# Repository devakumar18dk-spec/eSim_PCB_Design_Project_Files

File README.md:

<div align="center">

# ⚡ Enhanced Power Supply ESP32

### Wide-Input (7–24 V) ESP32-C3 Development Board — A Complete Embedded Hardware Platform

**Designed & Simulated in FOSSEE eSim (KiCad-based workflow)**

</div>

<br>

<p align="center"><sub>🧊 3D render of the routed 4-layer board — ESP32-C3-WROOM-02, USB-C, DC barrel jack, and dual GPIO headers.</sub></p>

<div align="center">

`Power In (7–24V)` → `Protection` → `5V Buck` → `3.3V LDO` → `ESP32-C3` ⚡

</div>

```bash
git clone https://github.com/devakumar18dk-spec/eSim_PCB_Design_Project_Files.git
```

---

## 📖 Table of Contents

- [Overview](#-overview)
- [Highlights & Features](#-highlights--features)
- [System Architecture](#-system-architecture)
- [Power Architecture](#-power-architecture)
- [USB-C Interface](#-usb-c-interface)
- [Boot & Reset Control](#-boot--reset-control)
- [RTC Timing](#-rtc-timing)
- [GPIO Expansion](#-gpio-expansion)
- [PCB Design (4-Layer)](#-pcb-design-4-layer)
- [📐 Schematic](#-schematic)
- [🖼 PCB Layout](#-pcb-layout)
- [Technical Specifications](#-technical-specifications)
- [Design Verification Checklist](#-design-verification-checklist)
- [Hardware Bring-Up Sequence](#-hardware-bring-up-sequence)
- [Design Workflow](#-design-workflow)
- [Repository Structure](#-repository-structure)
- [Getting Started](#-getting-started)
- [Contributing](#-contributing)
- [License](#-license)
- [Acknowledgements](#-acknowledgements)

---

## 🧭 Overview

This project presents the design and PCB implementation of a custom **ESP32-C3-based development board**, engineered end-to-end using the **FOSSEE eSim electronics design environment**. Rather than functioning as a simple ESP32 breakout, this board is architected as a **complete embedded hardware platform** — integrating wide-range DC power input, robust input protection, two-stage voltage regulation, USB-C connectivity with ESD protection, hardware boot/reset control, RTC timing, and expandable GPIO — all realized on a **four-layer PCB**.

> **Design philosophy:** protect first, convert efficiently, regulate cleanly, then compute. Every subsystem exists to deliver a stable, low-noise supply and a reliable interface to the ESP32-C3.

```
7–24 V DC  →  Protection  →  5 V Buck  →  3.3 V LDO  →  ESP32-C3
```

---

## ✨ Highlights & Features

<table>
<tr>
<td width="50%" valign="top">

### 🔋 Power System
- Wide **7 V – 24 V DC** input range
- Reverse-polarity protection via **P-channel MOSFET**
- **TVS/Zener** transient (surge) protection
- Two-stage regulation: **Buck (5 V) → LDO (3.3 V)**
- Local bulk + high-frequency decoupling at the MCU

### 🔌 Connectivity
- **USB Type-C** interface (16-pin receptacle)
- CC1/CC2 configuration resistors (device/sink mode)
- Dedicated **USBLC6-2SC6** ESD protection on D+/D−
- USB used strictly for data/programming — **not** primary power

</td>
<td width="50%" valign="top">

### 🧠 Control & Expansion
- **ESP32-C3-WROOM-02** central controller
- Dedicated **EN (Reset)** and **IO9 (Boot)** push buttons
- **32.768 kHz RTC crystal** for low-power timekeeping
- **2 × 8-pin, 2.54 mm** GPIO expansion headers

### 🧱 PCB Engineering
- **4-layer stack-up**: Power / Signal / Mixed / Ground
- Dedicated **ESP32 antenna keep-out zone**
- Functionally-grouped component placement
- Continuous ground plane for low-impedance return paths

</td>
</tr>
</table>

---

## 🏗 System Architecture

The board is organized into five functional sections: **Power**, **USB-C**, **Main Controller**, **Boot/Reset**, and **GPIO/Expansion**.

```
                  ESP32-C3 DEVELOPMENT BOARD
                           │
       ┌───────────────────┼───────────────────┐
       │                   │                   │
       ▼                   ▼                   ▼
 POWER SYSTEM         USB-C SYSTEM       CONTROL / I/O
       │                   │                   │
  7–24 V DC           USB Type-C          Boot Button
       │                   │               Reset Button
       ▼                   │                   │
 Input Protection          │                   │
       │                   │                   │
       ▼                   ▼                   ▼
 5 V Buck              ESD Protection      ESP32-C3
       │                   │                   │
       ▼                   ▼              GPIO Headers
 5 V Rail              USB D+/D−
       │
       ▼
 3.3 V LDO
       │
       ▼
  +3.3 V Rail
       │
       ▼
  ESP32-C3 WROOM-02
       │
       └── 32.768 kHz RTC Crystal
```

---

## 🔋 Power Architecture

Every subsystem on this board depends on a stable, protected supply — so power is treated as the primary design driver, not an afterthought.

### Main Power Path

```
DC Input → Protection → Buck Converter (5 V) → LDO (3.3 V) → ESP32-C3
```

The board deliberately avoids converting the full 7–24 V range directly to 3.3 V with a linear regulator. Instead, a **switching regulator** absorbs the large voltage difference efficiently, while an **LDO** performs final, low-noise regulation — the right tool for each job.

<details>
<summary><b>🛡️ Input Protection — click to expand</b></summary>

<br>

| Function | Component | Behavior |
|---|---|---|
| Transient protection | TVS / Zener network | Inactive under normal operation; clamps excess voltage during spikes |
| Reverse-polarity protection | P-channel MOSFET (STN3P6F6) | Low-resistance conduction on correct polarity; blocks reverse voltage |

```
Correct polarity          Incorrect polarity
      │                          │
      ▼                          ▼
P-MOSFET conducts          MOSFET blocks
      │                          │
      ▼                          ▼
Power reaches regulator    Downstream circuitry protected
```

A P-MOSFET is used instead of a conventional diode because it offers **much lower conduction loss**.

</details>

<details>
<summary><b>⚙️ 5 V Buck Conversion — click to expand</b></summary>

<br>

The protected input feeds the **LMR50410-Q1** switching regulator, which converts **7–24 V → 5 V** by transferring energy through controlled switching rather than dissipating the difference as heat.

**Supporting components:** 4.7 µH inductor · bootstrap capacitor · input/output capacitors · feedback resistor network · 10 µF local input capacitor (placed close to the regulator to keep the high-frequency current loop compact).

```
7–24 V ─► Switching Node ─► 4.7 µH Inductor ─► Output Filter ─► 5 V
```

</details>

<details>
<summary><b>🎯 3.3 V LDO Post-Regulation — click to expand</b></summary>

<br>

The 5 V rail feeds an **LM1117-3.3** LDO, which handles only the small **5 V → 3.3 V** step. This division of labor means:

| Stage | Responsibility |
|---|---|
| Buck | Efficient large voltage conversion (7–24 V → 5 V) |
| LDO | Final clean regulation, ripple attenuation, low-impedance supply |

The LDO also provides power-supply rejection within its effective PSRR band, attenuating residual switching ripple before it reaches the ESP32-C3.

</details>

<details>
<summary><b>📎 MCU Decoupling — click to expand</b></summary>

<br>

Local **4.7 µF** (bulk) and **100 nF** (high-frequency) capacitors sit right at the ESP32-C3 supply pins, supplying transient current locally instead of forcing it through long PCB traces from the regulator — reducing supply impedance seen by the controller.

</details>

<div align="right"><sub><a href="#-enhanced-power-supply-esp32">⬆ back to top</a></sub></div>

---

## 🔌 USB-C Interface

The USB-C section is an **independent communication interface**, cleanly separated from the main power path.

| Element | Detail |
|---|---|
| Connector | USB Type-C, 16-pin |
| CC configuration | 2 × 5.1 kΩ on CC1/CC2 → configures board as USB-C sink/device |
| ESD protection | USBLC6-2SC6, placed near the connector |
| Role | Data / programming only — **not** the primary power source |

```
External USB Connector → ESD Protection → ESP32-C3
```

Keeping USB power and main DC power separate lets the board run continuously from the 7–24 V input while still using USB freely for programming and debugging.

---

## 🛠 Boot & Reset Control

| Button | Signal | Function |
|---|---|---|
| Reset | EN | 10 kΩ pull-up; pressing forces EN low and resets the MCU |
| Boot | IO9 | 10 kΩ pull-up; pressing changes boot-strap state to enter programming mode |

```
USB connected → Hold BOOT → Reset ESP32-C3 → Enters programming mode
```

---

## ⏱ RTC Timing

A **32.768 kHz crystal** provides an external low-frequency timing reference for the ESP32-C3 RTC. It's placed close to the module to minimize parasitics and kept away from the buck converter's switching node to avoid noise coupling.

---

## 🧩 GPIO Expansion

Two **8-pin, 2.54 mm pitch headers** expose selected ESP32-C3 GPIOs, turning the board into a reusable development platform for sensors, LEDs, displays, communication modules, and breadboard prototyping.

---

## 🧱 PCB Design (4-Layer)

| Layer | Purpose |
|---|---|
| **F.Cu** (Top) | Power distribution & primary component routing |
| **In1.Cu** | Signal routing (GPIO fan-out from the ESP32-C3) |
| **In2.Cu** | Mixed-purpose routing / secondary distribution |
| **B.Cu** (Bottom) | Continuous ground plane |

<details>
<summary><b>📍 Component Placement Strategy</b></summary>

<br>

| Region | Contents | Rationale |
|---|---|---|
| Upper | ESP32-C3 module, antenna toward board edge | Unobstructed RF environment |
| Central | Buck converter, LDO, protection circuitry, USB-C | Short, low-impedance power connections |
| Lower | Boot/Reset buttons | User accessibility |
| Sides | GPIO headers (left & right) | Convenient external interfacing |

</details>

<details>
<summary><b>📡 Antenna Keep-Out</b></summary>

<br>

A clearly defined **keep-out zone** sits above the ESP32-C3 module — no copper, tracks, or vias are routed through this area, per module manufacturer guidance, to prevent detuning or shielding the integrated antenna.

</details>

<details>
<summary><b>🧵 Routing & Grounding Philosophy</b></summary>

<br>

- **High-current power paths** — short and comparatively wide (DC input, MOSFET, buck, inductor, 5 V rail, LDO)
- **Switching node** — kept as small as practical to limit EMI coupling
- **USB D+/D−** — routed as a matched differential pair, ESD device close to the connector
- **RTC crystal traces** — short, isolated from switching noise
- **Ground plane (B.Cu)** — continuous reference plane minimizing loop area, EMI, and supply noise — especially important given the ESP32-C3's onboard radio

</details>

<details>
<summary><b>🌡️ Thermal Considerations</b></summary>

<br>

Primary heat sources are the **buck converter**, **LDO**, and **protection MOSFET**. The LDO has the most predictable thermal profile since it dissipates the 5 V→3.3 V difference directly — adequate copper area is provided around its thermal pads per datasheet recommendations.

</details>

---

## 📐 Schematic

<div align="center">

| 🔋 Input → 5V → 3.3V | 🔌 USB-C & ESD | 🛠 Boot & Reset | 🧠 Main Controller | 🧩 GPIOs |
|:---:|:---:|:---:|:---:|:---:|
| ST6P3F6, LMR50410-Q1, LM1117-3.3 | USB-C receptacle, USBLC6-2SC6 | EN & IO9 push buttons | ESP32-C3-WROOM-02 | 2 × 8-pin headers |

</div>

<p align="center"><sub>📄 Captured entirely in <b>FOSSEE eSim</b> — five functional blocks laid out for clarity: power regulation (top), USB-C/protection, boot/reset, and GPIO breakout (bottom row), with the main ESP32-C3 controller on the right.</sub></p>

---

## 🖼 PCB Layout

The board is routed across **four copper layers**, each with a distinct role. Toggle through the stack below — every view shares the same silhouette so you can trace a single net (e.g. GND) from top to bottom.

<table align="center">
<tr>
<th align="center">🟥 F.Cu — Power / Top Layer</th>
<th align="center">🟩 In1.Cu — Signal Layer</th>
</tr>
<tr>
<td></td>
<td></td>
</tr>
<tr>
<td align="center"><sub>Primary power distribution & component-side routing</sub></td>
<td align="center"><sub>ESP32-C3 GPIO fan-out toward J3 / J4 headers</sub></td>
</tr>
<tr>
<th align="center">🟧 In2.Cu — Mixed Routing Layer</th>
<th align="center">🟦 B.Cu — Ground Plane</th>
</tr>
<tr>
<td></td>
<td></td>
</tr>
<tr>
<td align="center"><sub>Secondary power/signal distribution channel</sub></td>
<td align="center"><sub>Continuous ground reference plane</sub></td>
</tr>
</table>

> 🛰️ **Antenna Keep-Out Zone** — visible as the hatched `KEEP-OUT ZONE / Antenna` region above the ESP32-C3 module on every layer. No copper, tracks, or vias are routed through this area to protect RF performance.

<details>
<summary><b>📊 Routing Stats (from PCB editor)</b></summary>

<br>

| Metric | Count |
|---|---|
| Pads | 151 |
| Vias | 102 |
| Nets | 586 |
| Unrouted | 0 ✅ |

</details>

<div align="right"><sub><a href="#-enhanced-power-supply-esp32">⬆ back to top</a></sub></div>

---

## 📋 Technical Specifications

| Specification | Design |
|---|---|
| MCU | ESP32-C3-WROOM-02 |
| Main DC input | 7–24 V |
| Primary power connector | DC input connector |
| Input protection | TVS/Zener + P-channel MOSFET |
| Reverse polarity protection | STN3P6F6 P-MOSFET |
| Buck regulator | LMR50410-Q1 |
| Buck output | 5 V |
| Buck inductor | 4.7 µH |
| Post-regulator | LM1117-3.3 |
| Final logic rail | 3.3 V |
| RTC reference | 32.768 kHz crystal |
| USB connector | USB Type-C, 16-pin |
| USB CC resistors | 5.1 kΩ × 2 |
| USB ESD protection | USBLC6-2SC6 |
| Reset control | EN push button |
| Boot control | IO9 push button |
| Button pull-ups | 10 kΩ |
| GPIO expansion | 2 × 8-pin headers |
| GPIO header pitch | 2.54 mm |
| PCB structure | 4-layer |
| F.Cu | Primary power / component routing |
| In1.Cu | Signal routing |
| In2.Cu | Mixed routing / distribution |
| B.Cu | Ground plane |
| RF provision | ESP32 antenna keep-out |
| Design environment | FOSSEE eSim / KiCad-based workflow |

---

## ✅ Design Verification Checklist

<table>
<tr>
<td width="50%" valign="top">

**Schematic Checks**
- [ ] All power nets verified
- [ ] 3.3 V connections verified
- [ ] 5 V connections verified
- [ ] All ground connections verified
- [ ] ESP32-C3 power pins checked
- [ ] Boot strapping verified
- [ ] EN/reset circuitry verified
- [ ] USB D+/D− connections verified
- [ ] USB CC resistors verified
- [ ] No unintended VBUS-to-3.3 V paths

</td>
<td width="50%" valign="top">

**PCB Checks**
- [ ] Design Rule Check (DRC) passed
- [ ] Track widths verified
- [ ] Clearances verified
- [ ] Via placement checked
- [ ] Copper-zone connections checked
- [ ] Antenna keep-out respected
- [ ] Silkscreen overlaps checked
- [ ] Connector orientation verified
- [ ] Footprint pin numbering verified
- [ ] Mounting/mechanical dimensions verified

</td>
</tr>
</table>

<div align="right"><sub><a href="#-enhanced-power-supply-esp32">⬆ back to top</a></sub></div>

---

## 🧪 Hardware Bring-Up Sequence

> Do **not** connect the ESP32 module immediately after fabrication — follow a controlled sequence.

| Step | Test | Expected Result |
|---|---|---|
| 1 | Input protection | Protected input rail stable across 7–24 V |
| 2 | Buck converter | ~**+5 V** at buck output (before connecting downstream circuitry) |
| 3 | LDO | ~**+3.3 V** at LDO output |
| 4 | MCU power | ESP32-C3 receives correct 3.3 V supply |
| 5 | Reset | Pressing EN resets the MCU |
| 6 | Boot | IO9 + reset sequencing enters programming mode |
| 7 | USB | USB enumeration / programming succeeds |
| 8 | GPIO | Expansion headers verified with simple GPIO firmware |
| 9 | RTC | 32.768 kHz RTC functionality confirmed |

---

## 🔁 Design Workflow

```
System Requirements → Circuit Architecture → Component Selection
        → Schematic Capture (eSim) → Electrical Connectivity Verification
        → Footprint Assignment → PCB Layout → 4-Layer Stack-up
        → Component Placement → Power Routing → Signal Routing
        → Ground Plane → Antenna Keep-Out → Design Rule Check
        → Gerber / Manufacturing Files → PCB Fabrication → Hardware Testing
```

---

## 🗂 Repository Structure

```
eSim_PCB_Design_Project_Files/
├── assets/
│   └── images/
│       ├── board-render.png       # 3D render
│       ├── schematic.png          # Full eSim schematic
│       ├── pcb-layout-top.png     # F.Cu — power layer
│       ├── pcb-layout-in1.png     # In1.Cu — signal layer
│       ├── pcb-layout-in2.png     # In2.Cu — mixed layer
│       └── pcb-layout-bottom.png  # B.Cu — ground plane
├── hardware/
│   ├── schematic/          # eSim / KiCad schematic project files
│   ├── pcb/                # PCB layout project files
│   └── gerbers/            # Manufacturing output (Gerbers, drill files, BOM)
├── docs/
│   └── technical-report.md # Full design & verification report
├── firmware/                # (optional) example/bring-up firmware
├── LICENSE
└── README.md
```

---

## 🚀 Getting Started

1. **Clone the repository**
   ```bash
   git clone https://github.com/devakumar18dk-spec/eSim_PCB_Design_Project_Files.git
   cd eSim_PCB_Design_Project_Files
   ```
2. **Open the schematic/PCB** in FOSSEE eSim or KiCad from the `hardware/` directory.
3. **Review the Gerbers** in `hardware/gerbers/` before sending to fabrication.
4. **Follow the [Hardware Bring-Up Sequence](#-hardware-bring-up-sequence)** after assembly.
5. **Flash firmware** over USB-C once power rails are verified.

---

## 🤝 Contributing

Contributions, issues, and design suggestions are welcome! Feel free to open a pull request or start a discussion if you'd like to improve the power architecture, layout, or documentation.

---

## 📄 License

This project is released under the **MIT License** — see [`LICENSE`](LICENSE) for details. *(Update if a different license applies.)*

---

## 🙌 Acknowledgements

- **FOSSEE eSim** — schematic capture and simulation environment
- **KiCad** — PCB layout workflow
- **Espressif Systems** — ESP32-C3-WROOM-02 module

---

<div align="center">

### 🧩 Built as a complete embedded hardware platform — not just an ESP32 carrier board.

**Wide-range power management · Protection · Wireless processing · USB-C · Hardware boot control · RTC · Expandable I/O**
**— all in a single four-layer PCB.**

**⭐ If this project helped you, consider starring the repository!**

[⬆ Back to top](#-enhanced-power-supply-esp32)

</div>

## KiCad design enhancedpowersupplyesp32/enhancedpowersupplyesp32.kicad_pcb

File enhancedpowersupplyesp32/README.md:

<div align="center">

# ⚡ ESP32-C3 Wide-Input Development Board

### A Complete Embedded Hardware Platform — Not Just a Breakout Board

**Designed & Simulated in FOSSEE eSim (KiCad-based workflow)**

</div>

<br>

<p align="center"><sub>🧊 3D render of the routed 4-layer board — ESP32-C3-WROOM-02, USB-C, DC barrel jack, and dual GPIO headers.</sub></p>

<div align="center">

`Power In` → `Protection` → `5V Buck` → `3.3V LDO` → `ESP32-C3` ⚡

</div>

---

## 📖 Table of Contents

- [Overview](#-overview)
- [Highlights & Features](#-highlights--features)
- [System Architecture](#-system-architecture)
- [Power Architecture](#-power-architecture)
- [USB-C Interface](#-usb-c-interface)
- [Boot & Reset Control](#-boot--reset-control)
- [RTC Timing](#-rtc-timing)
- [GPIO Expansion](#-gpio-expansion)
- [PCB Design (4-Layer)](#-pcb-design-4-layer)
- [📐 Schematic](#-schematic)
- [🖼 PCB Layout](#-pcb-layout)
- [Technical Specifications](#-technical-specifications)
- [Design Verification Checklist](#-design-verification-checklist)
- [Hardware Bring-Up Sequence](#-hardware-bring-up-sequence)
- [Design Workflow](#-design-workflow)
- [Repository Structure](#-repository-structure)
- [Getting Started](#-getting-started)
- [Contributing](#-contributing)
- [License](#-license)
- [Acknowledgements](#-acknowledgements)

---

## 🧭 Overview

This project presents the design and PCB implementation of a custom **ESP32-C3-based development board**, engineered end-to-end using the **FOSSEE eSim electronics design environment**. Rather than functioning as a simple ESP32 breakout, this board is architected as a **complete embedded hardware platform** — integrating wide-range DC power input, robust input protection, two-stage voltage regulation, USB-C connectivity with ESD protection, hardware boot/reset control, RTC timing, and expandable GPIO — all realized on a **four-layer PCB**.

> **Design philosophy:** protect first, convert efficiently, regulate cleanly, then compute. Every subsystem exists to deliver a stable, low-noise supply and a reliable interface to the ESP32-C3.

```
7–24 V DC  →  Protection  →  5 V Buck  →  3.3 V LDO  →  ESP32-C3
```

---

## ✨ Highlights & Features

<table>
<tr>
<td width="50%" valign="top">

### 🔋 Power System
- Wide **7 V – 24 V DC** input range
- Reverse-polarity protection via **P-channel MOSFET**
- **TVS/Zener** transient (surge) protection
- Two-stage regulation: **Buck (5 V) → LDO (3.3 V)**
- Local bulk + high-frequency decoupling at the MCU

### 🔌 Connectivity
- **USB Type-C** interface (16-pin receptacle)
- CC1/CC2 configuration resistors (device/sink mode)
- Dedicated **USBLC6-2SC6** ESD protection on D+/D−
- USB used strictly for data/programming — **not** primary power

</td>
<td width="50%" valign="top">

### 🧠 Control & Expansion
- **ESP32-C3-WROOM-02** central controller
- Dedicated **EN (Reset)** and **IO9 (Boot)** push buttons
- **32.768 kHz RTC crystal** for low-power timekeeping
- **2 × 8-pin, 2.54 mm** GPIO expansion headers

### 🧱 PCB Engineering
- **4-layer stack-up**: Power / Signal / Mixed / Ground
- Dedicated **ESP32 antenna keep-out zone**
- Functionally-grouped component placement
- Continuous ground plane for low-impedance return paths

</td>
</tr>
</table>

---

## 🏗 System Architecture

The board is organized into five functional sections: **Power**, **USB-C**, **Main Controller**, **Boot/Reset**, and **GPIO/Expansion**.

```
                  ESP32-C3 DEVELOPMENT BOARD
                           │
       ┌───────────────────┼───────────────────┐
       │                   │                   │
       ▼                   ▼                   ▼
 POWER SYSTEM         USB-C SYSTEM       CONTROL / I/O
       │                   │                   │
  7–24 V DC           USB Type-C          Boot Button
       │                   │               Reset Button
       ▼                   │                   │
 Input Protection          │                   │
       │                   │                   │
       ▼                   ▼                   ▼
 5 V Buck              ESD Protection      ESP32-C3
       │                   │                   │
       ▼                   ▼              GPIO Headers
 5 V Rail              USB D+/D−
       │
       ▼
 3.3 V LDO
       │
       ▼
  +3.3 V Rail
       │
       ▼
  ESP32-C3 WROOM-02
       │
       └── 32.768 kHz RTC Crystal
```

---

## 🔋 Power Architecture

Every subsystem on this board depends on a stable, protected supply — so power is treated as the primary design driver, not an afterthought.

### Main Power Path

```
DC Input → Protection → Buck Converter (5 V) → LDO (3.3 V) → ESP32-C3
```

The board deliberately avoids converting the full 7–24 V range directly to 3.3 V with a linear regulator. Instead, a **switching regulator** absorbs the large voltage difference efficiently, while an **LDO** performs final, low-noise regulation — the right tool for each job.

<details>
<summary><b>🛡️ Input Protection — click to expand</b></summary>

<br>

| Function | Component | Behavior |
|---|---|---|
| Transient protection | TVS / Zener network | Inactive under normal operation; clamps excess voltage during spikes |
| Reverse-polarity protection | P-channel MOSFET (STN3P6F6) | Low-resistance conduction on correct polarity; blocks reverse voltage |

```
Correct polarity          Incorrect polarity
      │                          │
      ▼                          ▼
P-MOSFET conducts          MOSFET blocks
      │                          │
      ▼                          ▼
Power reaches regulator    Downstream circuitry protected
```

A P-MOSFET is used instead of a conventional diode because it offers **much lower conduction loss**.

</details>

<details>
<summary><b>⚙️ 5 V Buck Conversion — click to expand</b></summary>

<br>

The protected input feeds the **LMR50410-Q1** switching regulator, which converts **7–24 V → 5 V** by transferring energy through controlled switching rather than dissipating the difference as heat.

**Supporting components:** 4.7 µH inductor · bootstrap capacitor · input/output capacitors · feedback resistor network · 10 µF local input capacitor (placed close to the regulator to keep the high-frequency current loop compact).

```
7–24 V ─► Switching Node ─► 4.7 µH Inductor ─► Output Filter ─► 5 V
```

</details>

<details>
<summary><b>🎯 3.3 V LDO Post-Regulation — click to expand</b></summary>

<br>

The 5 V rail feeds an **LM1117-3.3** LDO, which handles only the small **5 V → 3.3 V** step. This division of labor means:

| Stage | Responsibility |
|---|---|
| Buck | Efficient large voltage conversion (7–24 V → 5 V) |
| LDO | Final clean regulation, ripple attenuation, low-impedance supply |

The LDO also provides power-supply rejection within its effective PSRR band, attenuating residual switching ripple before it reaches the ESP32-C3.

</details>

<details>
<summary><b>📎 MCU Decoupling — click to expand</b></summary>

<br>

Local **4.7 µF** (bulk) and **100 nF** (high-frequency) capacitors sit right at the ESP32-C3 supply pins, supplying transient current locally instead of forcing it through long PCB traces from the regulator — reducing supply impedance seen by the controller.

</details>

<div align="right"><sub><a href="#-esp32-c3-wide-input-development-board">⬆ back to top</a></sub></div>

---

## 🔌 USB-C Interface

The USB-C section is an **independent communication interface**, cleanly separated from the main power path.

| Element | Detail |
|---|---|
| Connector | USB Type-C, 16-pin |
| CC configuration | 2 × 5.1 kΩ on CC1/CC2 → configures board as USB-C sink/device |
| ESD protection | USBLC6-2SC6, placed near the connector |
| Role | Data / programming only — **not** the primary power source |

```
External USB Connector → ESD Protection → ESP32-C3
```

Keeping USB power and main DC power separate lets the board run continuously from the 7–24 V input while still using USB freely for programming and debugging.

---

## 🛠 Boot & Reset Control

| Button | Signal | Function |
|---|---|---|
| Reset | EN | 10 kΩ pull-up; pressing forces EN low and resets the MCU |
| Boot | IO9 | 10 kΩ pull-up; pressing changes boot-strap state to enter programming mode |

```
USB connected → Hold BOOT → Reset ESP32-C3 → Enters programming mode
```

---

## ⏱ RTC Timing

A **32.768 kHz crystal** provides an external low-frequency timing reference for the ESP32-C3 RTC. It's placed close to the module to minimize parasitics and kept away from the buck converter's switching node to avoid noise coupling.

---

## 🧩 GPIO Expansion

Two **8-pin, 2.54 mm pitch headers** expose selected ESP32-C3 GPIOs, turning the board into a reusable development platform for sensors, LEDs, displays, communication modules, and breadboard prototyping.

---

## 🧱 PCB Design (4-Layer)

| Layer | Purpose |
|---|---|
| **F.Cu** (Top) | Power distribution & primary component routing |
| **In1.Cu** | Signal routing (GPIO fan-out from the ESP32-C3) |
| **In2.Cu** | Mixed-purpose routing / secondary distribution |
| **B.Cu** (Bottom) | Continuous ground plane |

<details>
<summary><b>📍 Component Placement Strategy</b></summary>

<br>

| Region | Contents | Rationale |
|---|---|---|
| Upper | ESP32-C3 module, antenna toward board edge | Unobstructed RF environment |
| Central | Buck converter, LDO, protection circuitry, USB-C | Short, low-impedance power connections |
| Lower | Boot/Reset buttons | User accessibility |
| Sides | GPIO headers (left & right) | Convenient external interfacing |

</details>

<details>
<summary><b>📡 Antenna Keep-Out</b></summary>

<br>

A clearly defined **keep-out zone** sits above the ESP32-C3 module — no copper, tracks, or vias are routed through this area, per module manufacturer guidance, to prevent detuning or shielding the integrated antenna.

</details>

<details>
<summary><b>🧵 Routing & Grounding Philosophy</b></summary>

<br>

- **High-current power paths** — short and comparatively wide (DC input, MOSFET, buck, inductor, 5 V rail, LDO)
- **Switching node** — kept as small as practical to limit EMI coupling
- **USB D+/D−** — routed as a matched differential pair, ESD device close to the connector
- **RTC crystal traces** — short, isolated from switching noise
- **Ground plane (B.Cu)** — continuous reference plane minimizing loop area, EMI, and supply noise — especially important given the ESP32-C3's onboard radio

</details>

<details>
<summary><b>🌡️ Thermal Considerations</b></summary>

<br>

Primary heat sources are the **buck converter**, **LDO**, and **protection MOSFET**. The LDO has the most predictable thermal profile since it dissipates the 5 V→3.3 V difference directly — adequate copper area is provided around its thermal pads per datasheet recommendations.

</details>

---

## 📐 Schematic

<div align="center">

| 🔋 Input → 5V → 3.3V | 🔌 USB-C & ESD | 🛠 Boot & Reset | 🧠 Main Controller | 🧩 GPIOs |
|:---:|:---:|:---:|:---:|:---:|
| ST6P3F6, LMR50410-Q1, LM1117-3.3 | USB-C receptacle, USBLC6-2SC6 | EN & IO9 push buttons | ESP32-C3-WROOM-02 | 2 × 8-pin headers |

</div>

<p align="center"><sub>📄 Captured entirely in <b>FOSSEE eSim</b> — five functional blocks laid out for clarity: power regulation (top), USB-C/protection, boot/reset, and GPIO breakout (bottom row), with the main ESP32-C3 controller on the right.</sub></p>

---

## 🖼 PCB Layout

The board is routed across **four copper layers**, each with a distinct role. Toggle through the stack below — every view shares the same silhouette so you can trace a single net (e.g. GND) from top to bottom.

<table align="center">
<tr>
<th align="center">🟥 F.Cu — Power / Top Layer</th>
<th align="center">🟩 In1.Cu — Signal Layer</th>
</tr>
<tr>
<td></td>
<td></td>
</tr>
<tr>
<td align="center"><sub>Primary power distribution & component-side routing</sub></td>
<td align="center"><sub>ESP32-C3 GPIO fan-out toward J3 / J4 headers</sub></td>
</tr>
<tr>
<th align="center">🟧 In2.Cu — Mixed Routing Layer</th>
<th align="center">🟦 B.Cu — Ground Plane</th>
</tr>
<tr>
<td></td>
<td></td>
</tr>
<tr>
<td align="center"><sub>Secondary power/signal distribution channel</sub></td>
<td align="center"><sub>Continuous ground reference plane</sub></td>
</tr>
</table>

> 🛰️ **Antenna Keep-Out Zone** — visible as the hatched `KEEP-OUT ZONE / Antenna` region above the ESP32-C3 module on every layer. No copper, tracks, or vias are routed through this area to protect RF performance.

<details>
<summary><b>📊 Routing Stats (from PCB editor)</b></summary>

<br>

| Metric | Count |
|---|---|
| Pads | 151 |
| Vias | 102 |
| Nets | 586 |
| Unrouted | 0 ✅ |

</details>

<div align="right"><sub><a href="#-esp32-c3-wide-input-development-board">⬆ back to top</a></sub></div>

---

## 📋 Technical Specifications

| Specification | Design |
|---|---|
| MCU | ESP32-C3-WROOM-02 |
| Main DC input | 7–24 V |
| Primary power connector | DC input connector |
| Input protection | TVS/Zener + P-channel MOSFET |
| Reverse polarity protection | STN3P6F6 P-MOSFET |
| Buck regulator | LMR50410-Q1 |
| Buck output | 5 V |
| Buck inductor | 4.7 µH |
| Post-regulator | LM1117-3.3 |
| Final logic rail | 3.3 V |
| RTC reference | 32.768 kHz crystal |
| USB connector | USB Type-C, 16-pin |
| USB CC resistors | 5.1 kΩ × 2 |
| USB ESD protection | USBLC6-2SC6 |
| Reset control | EN push button |
| Boot control | IO9 push button |
| Button pull-ups | 10 kΩ |
| GPIO expansion | 2 × 8-pin headers |
| GPIO header pitch | 2.54 mm |
| PCB structure | 4-layer |
| F.Cu | Primary power / component routing |
| In1.Cu | Signal routing |
| In2.Cu | Mixed routing / distribution |
| B.Cu | Ground plane |
| RF provision | ESP32 antenna keep-out |
| Design environment | FOSSEE eSim / KiCad-based workflow |

---

## ✅ Design Verification Checklist

<table>
<tr>
<td width="50%" valign="top">

**Schematic Checks**
- [ ] All power nets verified
- [ ] 3.3 V connections verified
- [ ] 5 V connections verified
- [ ] All ground connections verified
- [ ] ESP32-C3 power pins checked
- [ ] Boot strapping verified
- [ ] EN/reset circuitry verified
- [ ] USB D+/D− connections verified
- [ ] USB CC resistors verified
- [ ] No unintended VBUS-to-3.3 V paths

</td>
<td width="50%" valign="top">

**PCB Checks**
- [ ] Design Rule Check (DRC) passed
- [ ] Track widths verified
- [ ] Clearances verified
- [ ] Via placement checked
- [ ] Copper-zone connections checked
- [ ] Antenna keep-out respected
- [ ] Silkscreen overlaps checked
- [ ] Connector orientation verified
- [ ] Footprint pin numbering verified
- [ ] Mounting/mechanical dimensions verified

</td>
</tr>
</table>

<div align="right"><sub><a href="#-esp32-c3-wide-input-development-board">⬆ back to top</a></sub></div>

---

## 🧪 Hardware Bring-Up Sequence

> Do **not** connect the ESP32 module immediately after fabrication — follow a controlled sequence.

| Step | Test | Expected Result |
|---|---|---|
| 1 | Input protection | Protected input rail stable across 7–24 V |
| 2 | Buck converter | ~**+5 V** at buck output (before connecting downstream circuitry) |
| 3 | LDO | ~**+3.3 V** at LDO output |
| 4 | MCU power | ESP32-C3 receives correct 3.3 V supply |
| 5 | Reset | Pressing EN resets the MCU |
| 6 | Boot | IO9 + reset sequencing enters programming mode |
| 7 | USB | USB enumeration / programming succeeds |
| 8 | GPIO | Expansion headers verified with simple GPIO firmware |
| 9 | RTC | 32.768 kHz RTC functionality confirmed |

---

## 🔁 Design Workflow

```
System Requirements → Circuit Architecture → Component Selection
        → Schematic Capture (eSim) → Electrical Connectivity Verification
        → Footprint Assignment → PCB Layout → 4-Layer Stack-up
        → Component Placement → Power Routing → Signal Routing
        → Ground Plane → Antenna Keep-Out → Design Rule Check
        → Gerber / Manufacturing Files → PCB Fabrication → Hardware Testing
```

---

## 🗂 Repository Structure

```
esp32-c3-wide-input-devboard/
├── assets/
│   └── images/
│       ├── board-render.png       # 3D render
│       ├── schematic.png          # Full eSim schematic
│       ├── pcb-layout-top.png     # F.Cu — power layer
│       ├── pcb-layout-in1.png     # In1.Cu — signal layer
│       ├── pcb-layout-in2.png     # In2.Cu — mixed layer
│       └── pcb-layout-bottom.png  # B.Cu — ground plane
├── hardware/
│   ├── schematic/          # eSim / KiCad schematic project files
│   ├── pcb/                # PCB layout project files
│   └── gerbers/            # Manufacturing output (Gerbers, drill files, BOM)
├── docs/
│   └── technical-report.md # Full design & verification report
├── firmware/                # (optional) example/bring-up firmware
├── LICENSE
└── README.md
```

---

## 🚀 Getting Started

1. **Clone the repository**
   ```bash
   git clone https://github.com/<your-username>/esp32-c3-wide-input-devboard.git
   ```
2. **Open the schematic/PCB** in FOSSEE eSim or KiCad from the `hardware/` directory.
3. **Review the Gerbers** in `hardware/gerbers/` before sending to fabrication.
4. **Follow the [Hardware Bring-Up Sequence](#-hardware-bring-up-sequence)** after assembly.
5. **Flash firmware** over USB-C once power rails are verified.

---

## 🤝 Contributing

Contributions, issues, and design suggestions are welcome! Feel free to open a pull request or start a discussion if you'd like to improve the power architecture, layout, or documentation.

---

## 📄 License

This project is released under the **MIT License** — see [`LICENSE`](LICENSE) for details. *(Update if a different license applies.)*

---

## 🙌 Acknowledgements

- **FOSSEE eSim** — schematic capture and simulation environment
- **KiCad** — PCB layout workflow
- **Espressif Systems** — ESP32-C3-WROOM-02 module

---

<div align="center">

### 🧩 Built as a complete embedded hardware platform — not just an ESP32 carrier board.

**Wide-range power management · Protection · Wireless processing · USB-C · Hardware boot control · RTC · Expandable I/O**
**— all in a single four-layer PCB.**

**⭐ If this project helped you, consider starring the repository!**

[⬆ Back to top](#-esp32-c3-wide-input-development-board)

</div>

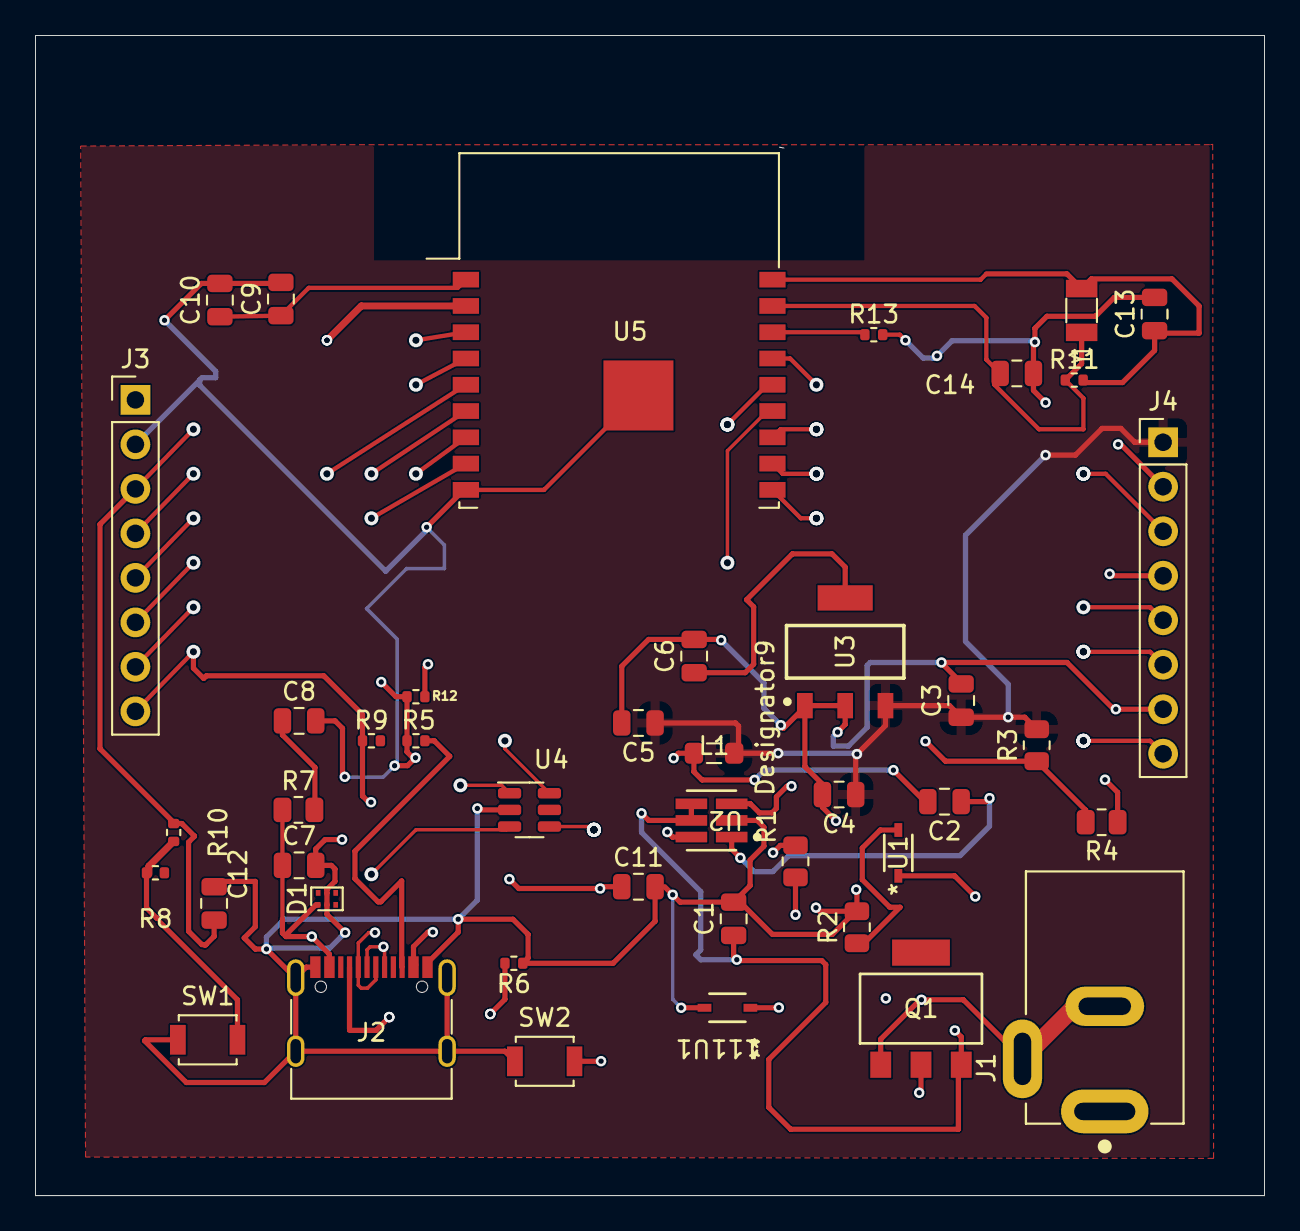
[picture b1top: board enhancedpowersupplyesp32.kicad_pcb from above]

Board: 4 copper layers, 70.2 x 66.2 mm, 43 parts (0 on the bottom side), 34 nets.

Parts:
111U1: 3.0SMCJ30A; SOD-323_1P8X1P35_ONS
C1, C5, C6: 10uF; C_0805_2012Metric
C2, C3: 100nF; C_0805_2012Metric
C4: 4.7uF; C_0805_2012Metric
C7, C8, C9, C13, C14: 4u7; C_0805_2012Metric
C10, C11, C12: 100n; C_0805_2012Metric
D1: PESD5V0L4UF; SOT-886
J1: EJ508B; CUI_PJ-202B
J2: USB_C_Receptacle_G-Switch_GT-USB-7010ASV
J3, J4: Conn_01x08_Male; PinHeader_1x08_P2.54mm_Vertical
L1: 4.7uF; L_0805_2012Metric_Pad1.05x1.20mm_HandSolder
Q1: STN3P6F6; SOT223_STN3_STM
R1: F100; R_0805_2012Metric
R2: 100k; R_0805_2012Metric
R3: 88.7k; R_0805_2012Metric
R4: 22.1k; R_0805_2012Metric
R5, R6, R11: 5k1; R_0402_1005Metric
R7: 0R; R_0805_2012Metric
R8, R9, R12, R13: 10k; R_0402_1005Metric
R10: 100k; R_0402_1005Metric
SW1, SW2: SW_Push; SW_SPST_B3U-1000P
U1: MM3Z12VT1; SOD-323_1P8X1P35_ONS
U2: LMR50410YQDBVRQ1; DBV0006A-IPC_A
U3: LM1117MPX-3.3_NOPB; DCY0004A_L
U4: USBLC6-2SC6; SOT-23-6
U5: ESP32-C3-WROOM-02-N4; ESP-WROOM-02
Y1: Crystal; Crystal_SMD_3215-2Pin_3.2x1.5mm

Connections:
+5V: C3.1 (A), C4.1 (A), C5.1 (A), J4.1, L1.1 (A), R3.2, U3.3 (INPUT)
/D+: J2.A6 (D+), J2.B6 (D+), U4.1 (I/O1)
/D-: J2.A7 (D-), J2.B7 (D-), U4.6 (I/O1)
/Vin: J1.1, R1.1
/Vin_F: C1.1, Q1.3 (S), U1.1 (K), U2.4 (EN), U2.5 (VIN)
EN: C12.1, J3.3, R10.1, U5.2 (EN)
GND: 111U1.2 (A), C1.2, C3.2 (B), C4.2 (B), C5.2 (B), C6.2 (B), C7.2, C8.2, C9.2, C10.2, C11.2, C12.2, C13.2, C14.2, D1.2 (A), D1.5 (A), J1.2, J1.3, J2.A1 (GND), J2.A12 (GND), J2.B1 (GND), J2.B12 (GND), J2.S1 (SHIELD), J3.2, J4.2, J4.4, J4.7, Q1.1 (G), R2.2, R4.1, R5.1, R6.1, R12.2, R13.2, SW1.1, SW2.1, U2.2 (GND), U3.1 (GND), U3.2 (OUT), U4.2 (GND), U5.9 (GND), U5.19 (GND)
I02: R13.1, U5.16 (IO2)
I03: J4.3, U5.15 (IO3)
I04: J3.4, U5.3 (IO4)
I05: J3.5, U5.4 (IO5)
I06: J3.6, U5.5 (IO6)
I07: J3.7, U5.6 (IO7)
I08: R12.1, U5.7 (IO8)
I09: C11.1, J3.8, R9.1, SW2.2, U5.8 (IO9)
I010: J4.8, U5.10 (IO10)
unnamed: 111U1.1 (K), Q1.2 (D), R1.2
unnamed: C2.1 (A), U2.1 (CB)
unnamed: C2.2 (B), L1.2 (B), U2.6 (SW)
unnamed: C6.1 (A), U3.4 (OUT)
unnamed: C8.1, R7.2
unnamed: C9.1, C10.1, U5.1 (3V3)
unnamed: C13.1, R11.2, U5.18 (IO0), Y1.1
unnamed: C14.1, R11.1, U5.17 (IO1), Y1.2
unnamed: J2.A5 (CC1), R6.2
unnamed: J2.B5 (CC2), R5.2
unnamed: R2.1, U1.2 (A)
unnamed: R3.1, R4.2, U2.3 (FB)
unnamed: R8.1, R10.2, SW1.2
RX: J4.6, U5.11 (RXD)
TX: J4.5, U5.12 (TXD)
USB_D+: U4.3 (I/O2), U5.14 (IO19)
USB_D-: U4.4 (I/O2), U5.13 (IO18)
VBUS: C7.1, D1.1 (K1), J2.A4 (VBUS), J2.A9 (VBUS), J2.B4 (VBUS), J2.B9 (VBUS), R7.1

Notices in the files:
README.md:
License: MIT
